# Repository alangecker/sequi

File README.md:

# sequi
_a arduino based solar tracker_

## BOM

|Count|Product|
|----|---|
|1|**Arduino Nano**|
|1|**DS3231 Module**
|1|**Mini Step Down 12-24V -> 5V 3A**
|4|**Relay 5V SRD-C**
|1|ULN2803A Darlington Driver|
|1|LM4040DBZ-4.1 Voltage Reference|
|3|1μF Capacitor 0805|
|1|0.1μF Capacitor 0805|
|3|100Ω Resistor 0805|
|1|1kΩ Resistor 0805|
|1|10kΩ Resistor 0805|
|1|SMAJ5.0A Diode|
|1|SMAJ24A Diode|
|1|1A Fuse 1206|
|1|5A Fuse ATO|
|3|_5.08mm 2pin terminal plug (optional)_|
|3|_3.5mm 3pin terminal plug (optional)_|
|1|_3.5mm 2pin terminal plug (optional)_|

## License
Copyright (C) 2019 Andreas Langecker

This program is free software: you can redistribute it and/or modify
it under the terms of the GNU General Public License as published by
the Free Software Foundation, either version 3 of the License, or
(at your option) any later version.

This program is distributed in the hope that it will be useful,
but WITHOUT ANY WARRANTY; without even the implied warranty of
MERCHANTABILITY or FITNESS FOR A PARTICULAR PURPOSE.  See the
GNU General Public License for more details.

You should have received a copy of the GNU General Public License
along with this program.  If not, see <http://www.gnu.org/licenses/>.

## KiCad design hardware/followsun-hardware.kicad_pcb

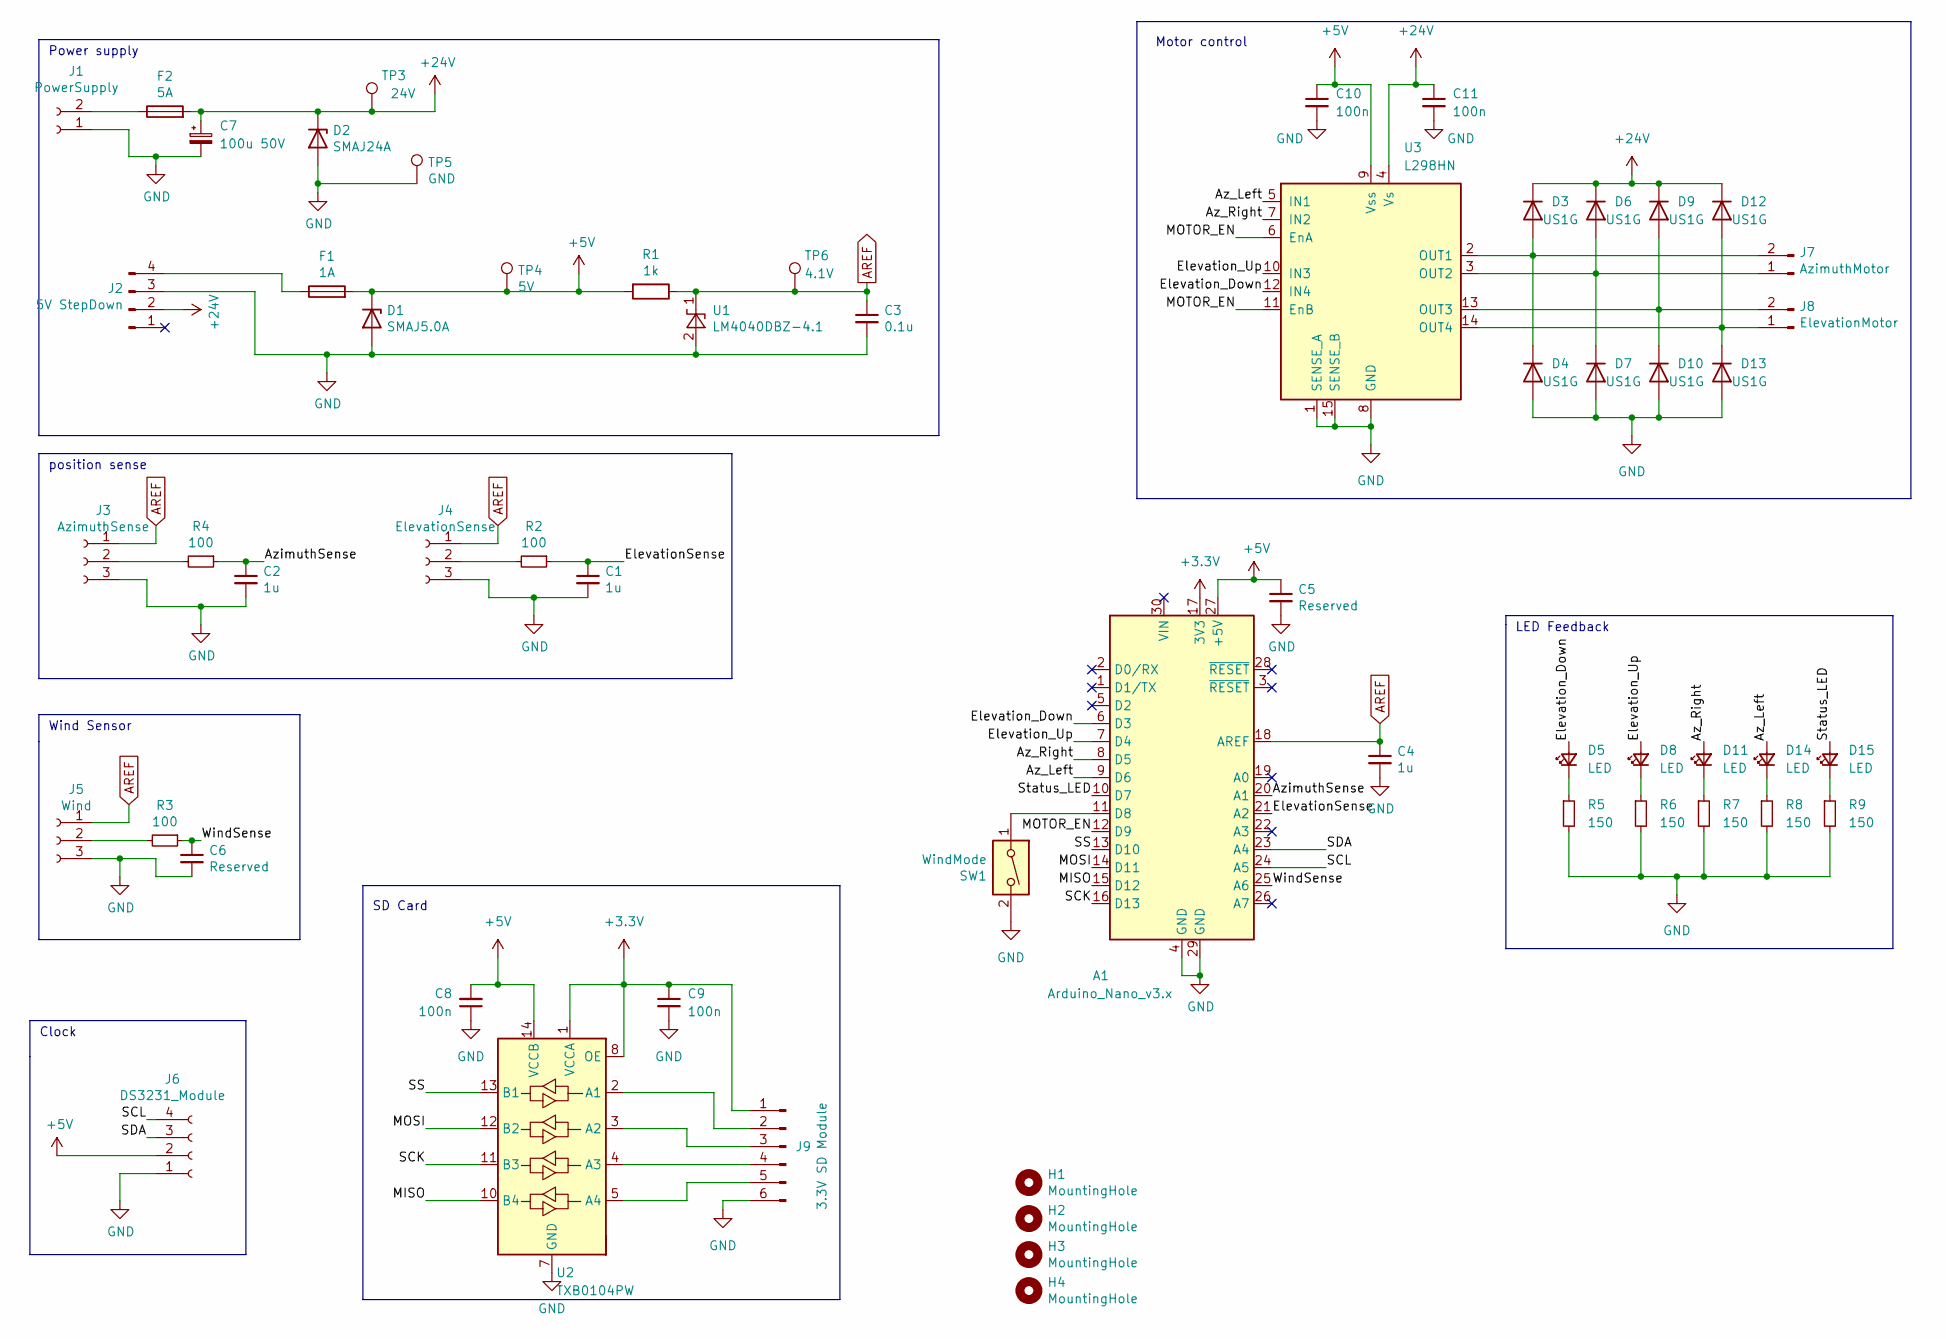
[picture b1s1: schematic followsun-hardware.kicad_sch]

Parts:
A1: Arduino_Nano_v3.x; Arduino_Nano
C1, C2, C4: 1u; C_0805_2012Metric_Pad1.18x1.45mm_HandSolder
C3: 0.1u; C_0805_2012Metric_Pad1.18x1.45mm_HandSolder
C5, C6: Reserved; C_0805_2012Metric_Pad1.18x1.45mm_HandSolder
C7: 100u 50V; CP_Radial_D8.0mm_P3.50mm
C8, C9, C10, C11: 100n; C_0805_2012Metric_Pad1.18x1.45mm_HandSolder
D1: SMAJ5.0A; D_SMA_Handsoldering
D2: SMAJ24A; D_SMA_Handsoldering
D3, D4, D6, D7, D9, D10, D12, D13: US1G; D_SMA
D5, D8, D11, D14, D15: LED; LED_1206_3216Metric_Pad1.42x1.75mm_HandSolder
F1: 1A; Fuse_1206_3216Metric_Pad1.42x1.75mm_HandSolder
F2: 5A; Fuse_Blade_ATO_directSolder
H1, H2, H3, H4: MountingHole; MountingHole_3mm_Pad_Via
J1: PowerSupply; TerminalBlock_bornier-2_P5.08mm
J2: 5V StepDown; MiniStepDown
J3: AzimuthSense; TerminalBlock_4Ucon_1x03_P3.50mm_Horizontal
J4: ElevationSense; TerminalBlock_4Ucon_1x03_P3.50mm_Horizontal
J5: Wind; TerminalBlock_4Ucon_1x03_P3.50mm_Horizontal
J6: DS3231_Module
J7: AzimuthMotor; TerminalBlock_bornier-2_P5.08mm
J8: ElevationMotor; TerminalBlock_bornier-2_P5.08mm
J9: 3.3V SD Module; PinHeader_1x06_P2.54mm_Vertical
R1: 1k; R_0805_2012Metric_Pad1.20x1.40mm_HandSolder
R2, R3, R4: 100; R_0805_2012Metric_Pad1.20x1.40mm_HandSolder
R5, R6, R7, R8, R9: 150; R_0805_2012Metric_Pad1.20x1.40mm_HandSolder
SW1: WindMode; TerminalBlock_4Ucon_1x02_P3.50mm_Horizontal
TP3: 24V; TestPoint_THTPad_D2.0mm_Drill1.0mm
TP4: 5V; TestPoint_THTPad_D2.0mm_Drill1.0mm
TP5: GND; TestPoint_THTPad_D2.0mm_Drill1.0mm
TP6: 4.1V; TestPoint_THTPad_D2.0mm_Drill1.0mm
U1: LM4040DBZ-4.1; SOT-23
U2: TXB0104PW; TSSOP-14_4.4x5mm_P0.65mm
U3: L298HN; TO-220-15_P2.54x2.54mm_StaggerOdd_Lead4.58mm_Vertical

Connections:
+3V3: A1.17 (3V3), C9.1, J9.1, U2.1 (VCCA), U2.8 (OE)
+5V: A1.27 (+5V), C5.1, C8.2, C10.1, D1.1 (K), F1.2, J6.2, R1.2, TP4.1, U2.14 (VCCB), U3.9 (Vss)
+24V: C7.1, C11.1, D2.1 (K), D3.1 (K), D6.1 (K), D9.1 (K), D12.1 (K), F2.2, J2.2, TP3.1, U3.4 (Vs)
/Az_Left: A1.9 (D6), D14.2 (A), U3.5 (IN1)
/Az_Right: A1.8 (D5), D11.2 (A), U3.7 (IN2)
/AzimuthSense: A1.20 (A1), C2.1, R4.1
/ElevationSense: A1.21 (A2), C1.1, R2.1
/Elevation_Down: A1.6 (D3), D5.2 (A), U3.12 (IN4)
/Elevation_Up: A1.7 (D4), D8.2 (A), U3.10 (IN3)
/MISO: A1.15 (D12), U2.10 (B4)
/MOSI: A1.14 (D11), U2.12 (B2)
/MOTOR_EN: A1.12 (D9), U3.6 (EnA), U3.11 (EnB)
/SCK: A1.16 (D13), U2.11 (B3)
/SCL: A1.24 (A5), J6.4
/SDA: A1.23 (A4), J6.3
/SS: A1.13 (D10), U2.13 (B1)
/Status_LED: A1.10 (D7), D15.2 (A)
/WindSense: A1.25 (A6), C6.1, R3.1
AREF: A1.18 (AREF), C3.1, C4.1, J3.1, J4.1, J5.1, R1.1, TP6.1, U1.1 (K)
GND: A1.4 (GND), A1.29 (GND), C1.2, C2.2, C3.2, C4.2, C5.2, C6.2, C7.2, C8.1, C9.2, C10.2, C11.2, D1.2 (A), D2.2 (A), D4.2 (A), D7.2 (A), D10.2 (A), D13.2 (A), J1.1, J2.3, J3.3, J4.3, J5.3, J6.1, J9.6, R5.2, R6.2, R7.2, R8.2, R9.2, SW1.2, TP5.1, U1.2 (A), U2.7 (GND), U3.1 (SENSE_A), U3.8 (GND), U3.15 (SENSE_B)
unnamed: A1.11 (D8), SW1.1
unnamed: D3.2 (A), D4.1 (K), J7.2, U3.2 (OUT1)
unnamed: D5.1 (K), R5.1
unnamed: D6.2 (A), D7.1 (K), J7.1, U3.3 (OUT2)
unnamed: D8.1 (K), R6.1
unnamed: D9.2 (A), D10.1 (K), J8.2, U3.13 (OUT3)
unnamed: D11.1 (K), R7.1
unnamed: D12.2 (A), D13.1 (K), J8.1, U3.14 (OUT4)
unnamed: D14.1 (K), R8.1
unnamed: D15.1 (K), R9.1
unnamed: F1.1, J2.4
unnamed: F2.1, J1.2
unnamed: J3.2, R4.2
unnamed: J4.2, R2.2
unnamed: J5.2, R3.2
unnamed: J9.2, U2.2 (A1)
unnamed: J9.3, U2.3 (A2)
unnamed: J9.4, U2.4 (A3)
unnamed: J9.5, U2.5 (A4)

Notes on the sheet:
LED Feedback
Wind Sensor
Motor control
Power supply
position sense
SD Card
Clock

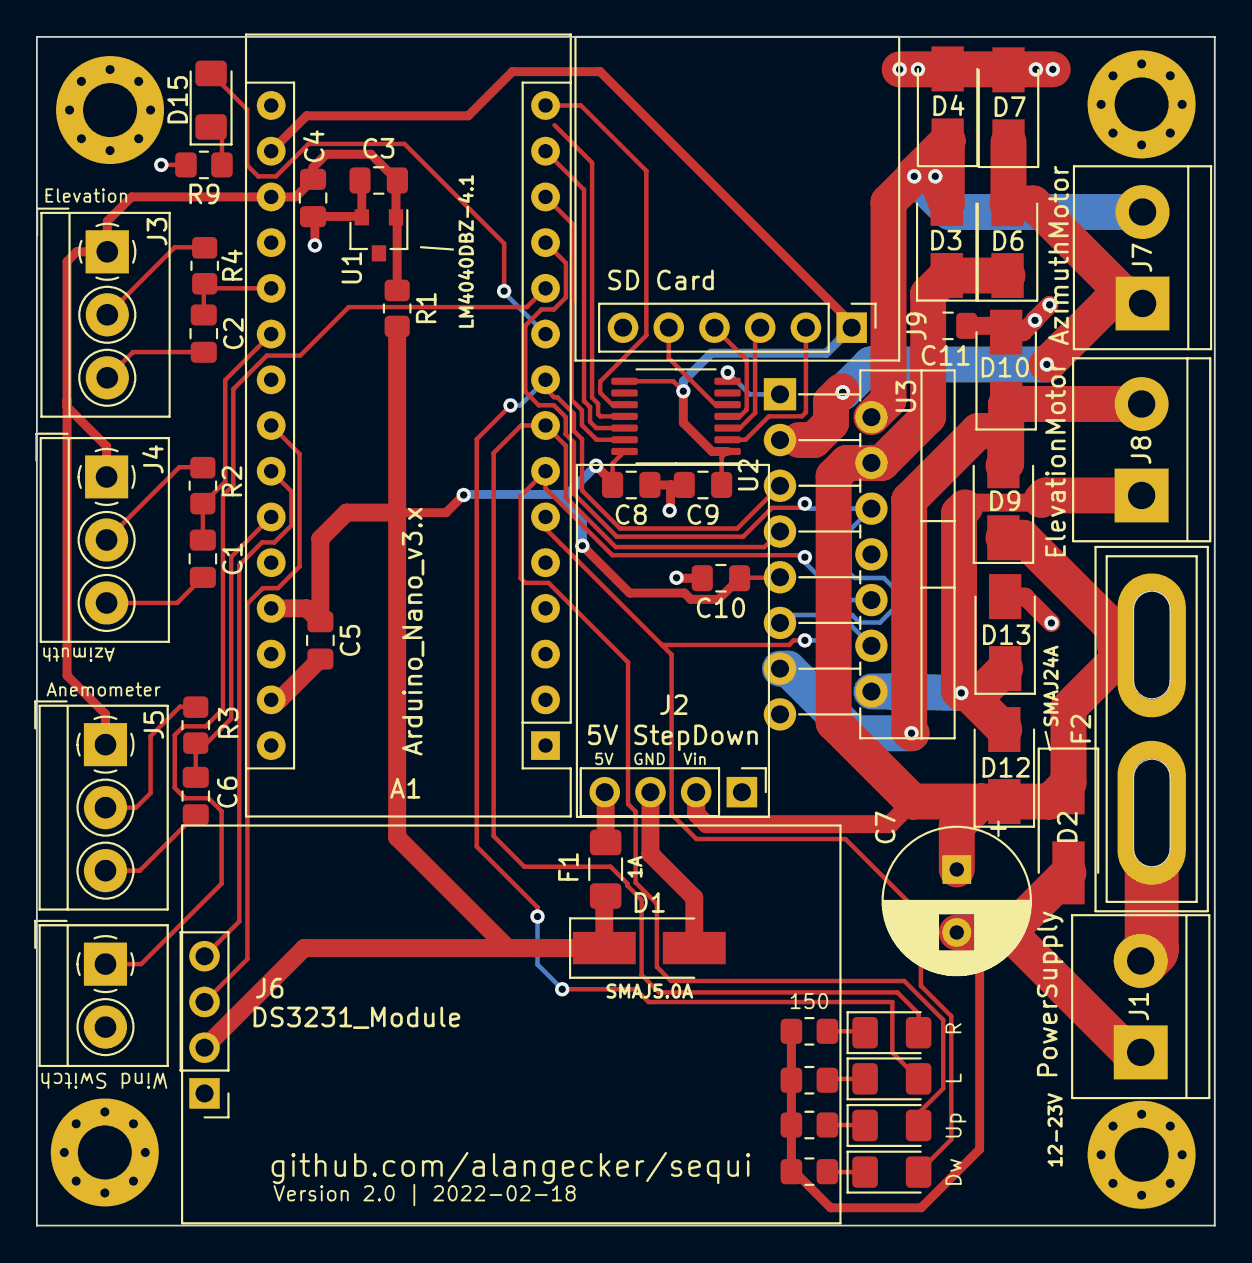
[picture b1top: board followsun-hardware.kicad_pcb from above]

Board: 2 copper layers, 65.4 x 66.0 mm, 55 parts (0 on the bottom side), 39 nets.

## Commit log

2019-11-10 added README.md
2019-12-26 software with consts for plant A
2022-01-27 v1.0
2022-02-18 major update with L298, sd cards, LEDs
